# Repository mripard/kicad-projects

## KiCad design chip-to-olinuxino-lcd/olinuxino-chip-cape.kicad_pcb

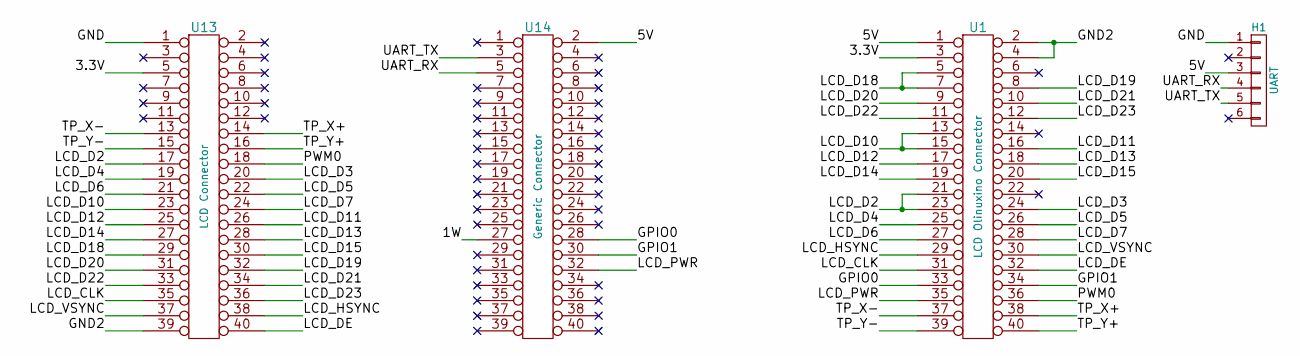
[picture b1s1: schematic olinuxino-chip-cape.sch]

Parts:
H1: UART; Pin_Header_Straight_1x06
U1: LCD Olinuxino Connector; Pin_Header_Straight_2x20
U13: LCD Connector; Pin_Header_Straight_2x20
U14: Generic Connector; Pin_Header_Straight_2x20

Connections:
/1W: U14.27
/3.3V: U1.3, U13.5
/5V: H1.3, U1.1, U14.2
/GND: H1.1, U13.1
/GND2: U1.2, U1.4, U13.39
/GPIO0: U1.33, U14.28
/GPIO1: U1.34, U14.30
/LCD_CLK: U1.31, U13.35
/LCD_D2: U1.21, U1.23, U13.17
/LCD_D3: U1.24, U13.20
/LCD_D4: U1.25, U13.19
/LCD_D5: U1.26, U13.22
/LCD_D6: U1.27, U13.21
/LCD_D7: U1.28, U13.24
/LCD_D10: U1.13, U1.15, U13.23
/LCD_D11: U1.16, U13.26
/LCD_D12: U1.17, U13.25
/LCD_D13: U1.18, U13.28
/LCD_D14: U1.19, U13.27
/LCD_D15: U1.20, U13.30
/LCD_D18: U1.5, U1.7, U13.29
/LCD_D19: U1.8, U13.32
/LCD_D20: U1.9, U13.31
/LCD_D21: U1.10, U13.34
/LCD_D22: U1.11, U13.33
/LCD_D23: U1.12, U13.36
/LCD_DE: U1.32, U13.40
/LCD_HSYNC: U1.29, U13.38
/LCD_PWR: U1.35, U14.32
/LCD_VSYNC: U1.30, U13.37
/PWM0: U1.36, U13.18
/TP_X+: U1.38, U13.14
/TP_X-: U1.37, U13.13
/TP_Y+: U1.40, U13.16
/TP_Y-: U1.39, U13.15
/UART_RX: H1.4, U14.5
/UART_TX: H1.5, U14.3

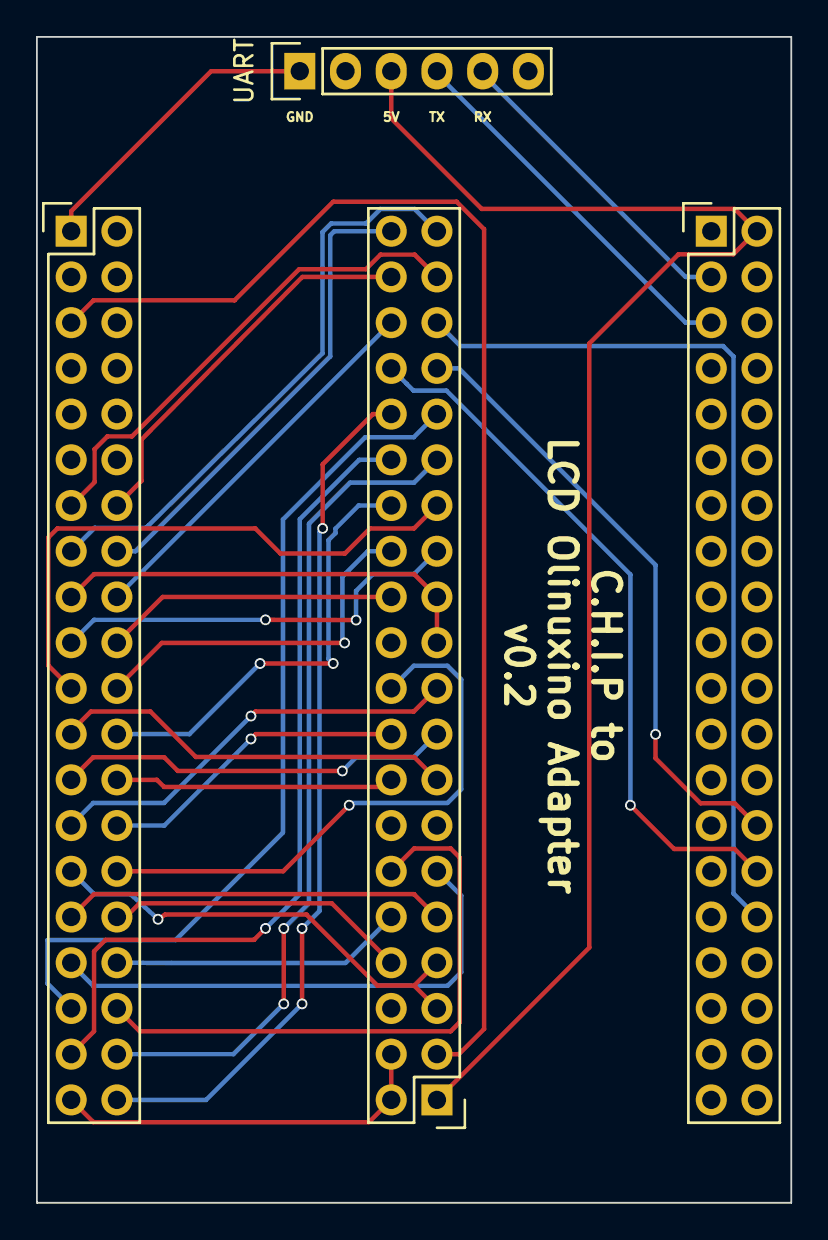
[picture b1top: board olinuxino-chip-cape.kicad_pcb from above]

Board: 2 copper layers, 41.9 x 64.8 mm, 4 parts (0 on the bottom side), 36 nets.

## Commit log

2015-10-13 Add Kicad files for the CHIP to olinuxino LCD
2015-10-13 License under the CC-BY-SA 4.0
2015-10-21 rerouting
2015-10-23 turn the connector around, and reroute
